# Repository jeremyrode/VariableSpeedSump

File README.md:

# VariableSpeedSump
Raspberry Pi Pico Based Variable Speed Sump Pump Controller

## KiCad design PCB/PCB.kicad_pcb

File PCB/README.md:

#  PCB

Fabricated on 8/18/2025

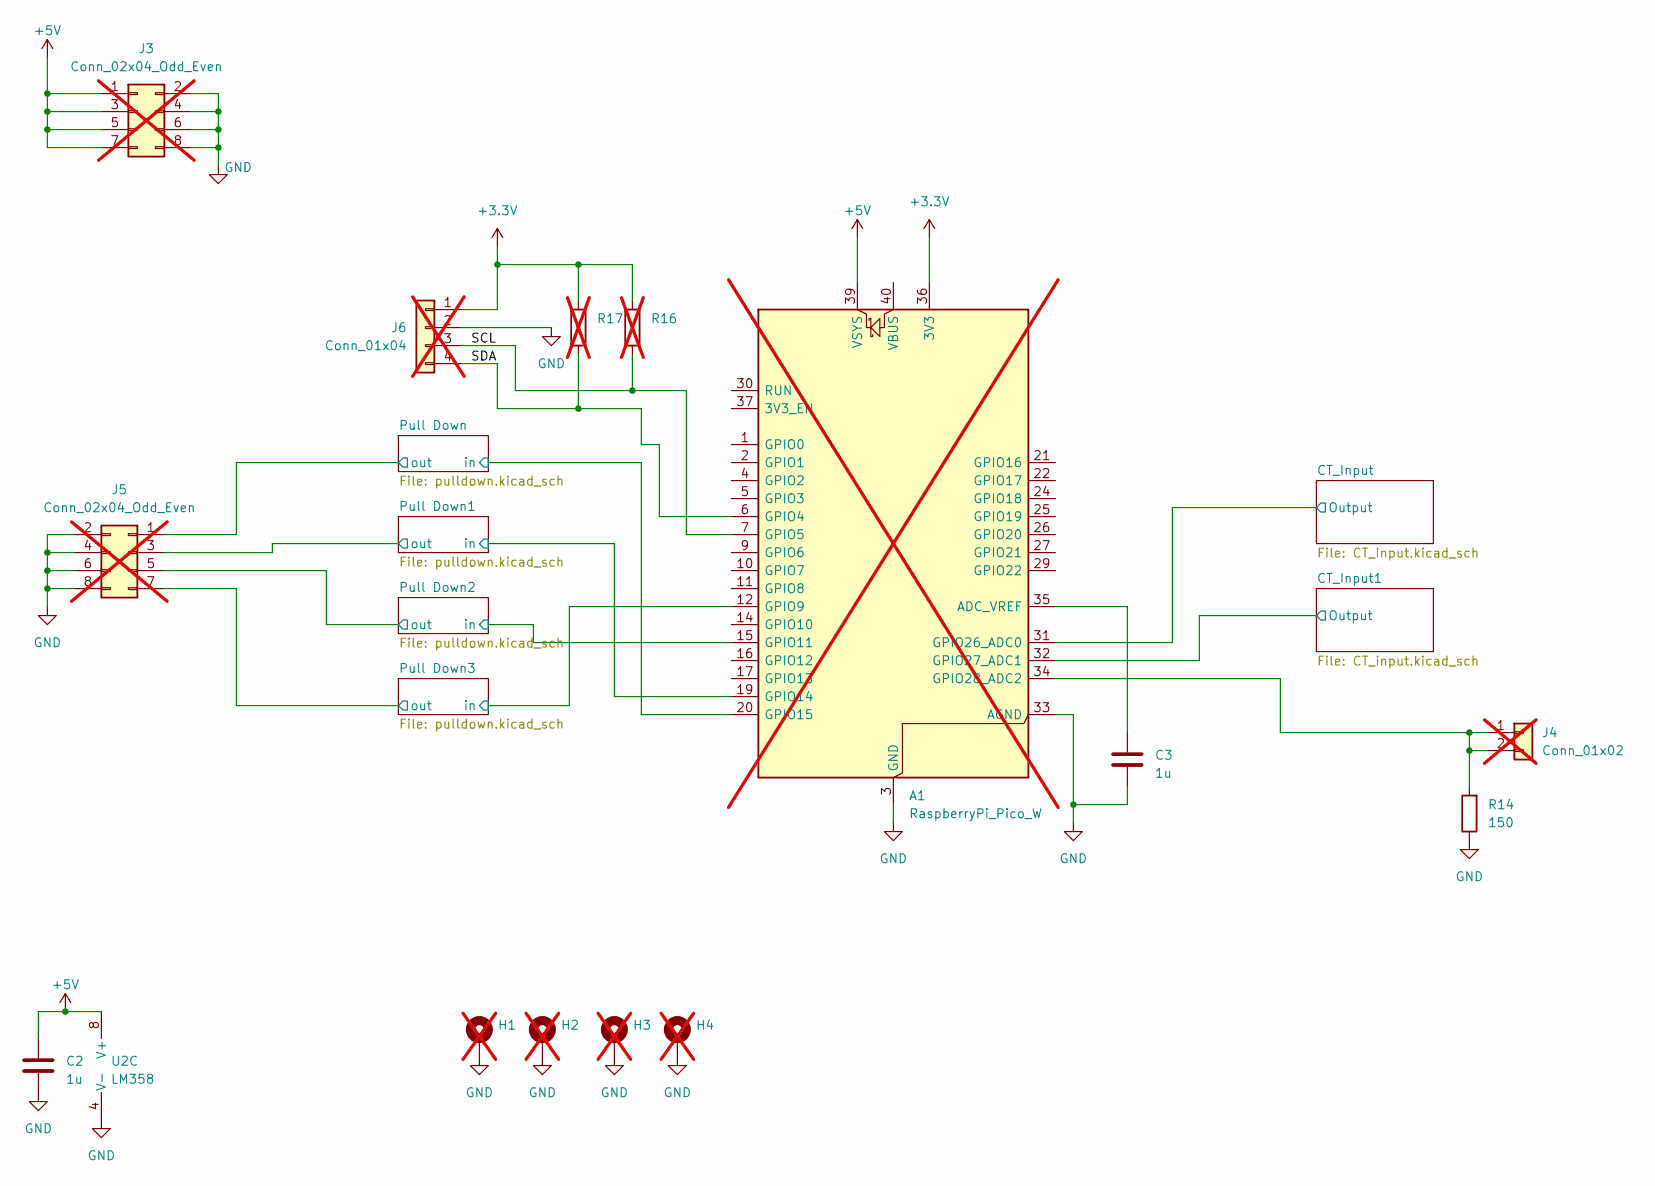
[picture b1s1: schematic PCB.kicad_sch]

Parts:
A1: RaspberryPi_Pico_W; RaspberryPi_Pico_Common_THT; not fitted
C2, C3: 1u; C_0805_2012Metric_Pad1.18x1.45mm_HandSolder
H1, H2, H3, H4: MountingHole_Pad; MountingHole_2.7mm_M2.5_Pad; not fitted
J3, J5: Conn_02x04_Odd_Even; PinHeader_2x04_P2.54mm_Vertical; not fitted
J4: Conn_01x02; PinHeader_1x02_P2.54mm_Vertical; not fitted
J6: Conn_01x04; PinHeader_1x04_P2.54mm_Vertical; not fitted
R14: 150; R_0805_2012Metric_Pad1.20x1.40mm_HandSolder
R16, R17: R_0805_2012Metric_Pad1.20x1.40mm_HandSolder; not fitted
U2: LM358; SOIC-8_3.9x4.9mm_P1.27mm

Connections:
+3.3V: A1.36 (3V3), J6.1, R16.2, R17.1
+5V: A1.39 (VSYS), C2.1, J3.1, J3.3, J3.5, J3.7, U2.8 (V+)
/CT_Input1/Output: A1.32 (GPIO27_ADC1); also elsewhere on the board
/CT_Input/Output: A1.31 (GPIO26_ADC0); also elsewhere on the board
/Pull Down1/in: A1.19 (GPIO14); also elsewhere on the board
/Pull Down1/out: J5.3; also elsewhere on the board
/Pull Down2/in: A1.15 (GPIO11); also elsewhere on the board
/Pull Down2/out: J5.5; also elsewhere on the board
/Pull Down3/in: A1.12 (GPIO9); also elsewhere on the board
/Pull Down3/out: J5.7; also elsewhere on the board
/Pull Down/in: A1.20 (GPIO15); also elsewhere on the board
/Pull Down/out: J5.1; also elsewhere on the board
/SCL: A1.7 (GPIO5), J6.3, R16.1
/SDA: A1.6 (GPIO4), J6.4, R17.2
GND: A1.3 (GND), A1.8 (GND), A1.13 (GND), A1.18 (GND), A1.23 (GND), A1.28 (GND), A1.33 (AGND), A1.38 (GND), C2.2, C3.2, H1.1, H2.1, H3.1, H4.1, J3.2, J3.4, J3.6, J3.8, J5.2, J5.4, J5.6, J5.8, J6.2, R14.1, U2.4 (V-); also elsewhere on the board
unnamed: A1.35 (ADC_VREF), C3.1
unnamed: A1.34 (GPIO28_ADC2), J4.1, J4.2, R14.2
unnamed 18: U2.7; also elsewhere on the board
unnamed 25: U2.5 (+); also elsewhere on the board
unnamed 26: U2.6 (-); also elsewhere on the board

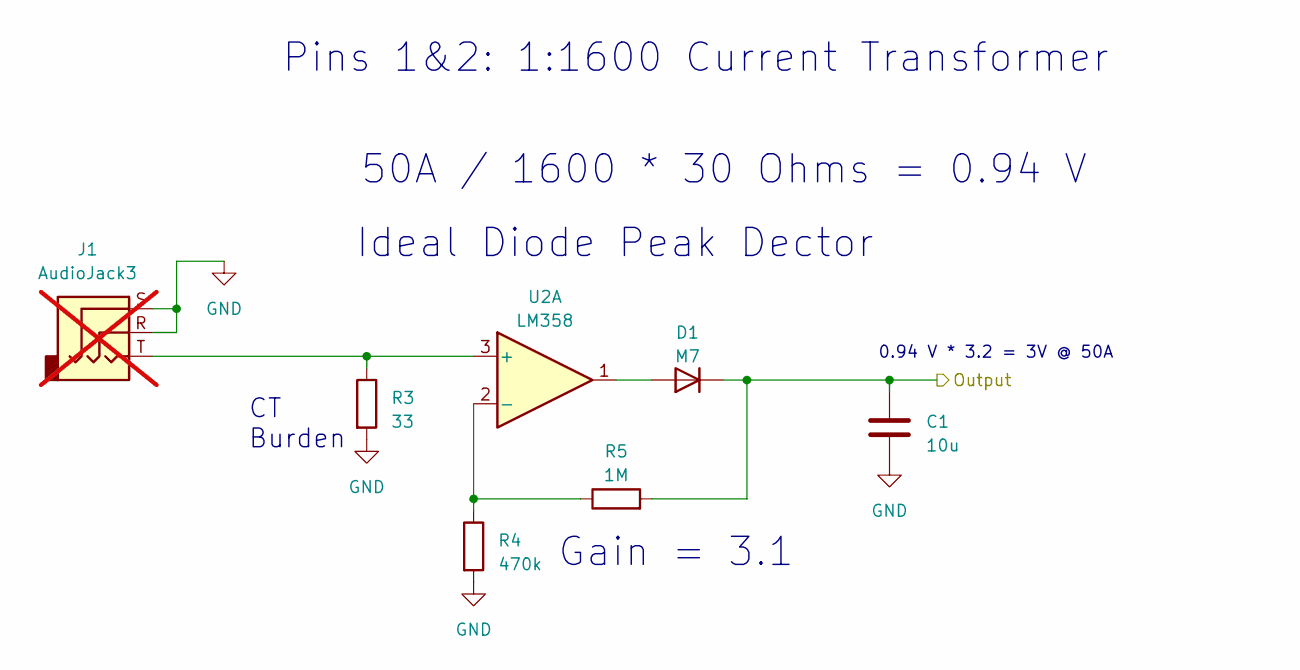
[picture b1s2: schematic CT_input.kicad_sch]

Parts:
C1: 10u; C_0805_2012Metric_Pad1.18x1.45mm_HandSolder
D1: M7; D_SMA
J1: AudioJack3; Jack_3.5mm_CUI_SJ1-3533NG_Horizontal; not fitted
R3: 33; R_0805_2012Metric_Pad1.20x1.40mm_HandSolder
R4: 470k; R_0805_2012Metric_Pad1.20x1.40mm_HandSolder
R5: 1M; R_0805_2012Metric_Pad1.20x1.40mm_HandSolder
U2: LM358; SOIC-8_3.9x4.9mm_P1.27mm

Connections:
/CT_Input/Output: C1.1, D1.1 (K), R5.2; also elsewhere on the board
GND: C1.2, J1.R, J1.S, R3.2, R4.2; also elsewhere on the board
unnamed: D1.2 (A), U2.1
unnamed 18: U2.7; also elsewhere on the board
unnamed: J1.T, R3.1, U2.3 (+)
unnamed: R4.1, R5.1, U2.2 (-)
unnamed 25: U2.5 (+); also elsewhere on the board
unnamed 26: U2.6 (-); also elsewhere on the board

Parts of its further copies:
C4: 10u; C_0805_2012Metric_Pad1.18x1.45mm_HandSolder
D2: M7; D_SMA
J2: AudioJack3; Jack_3.5mm_CUI_SJ1-3533NG_Horizontal; not fitted
R1: 33; R_0805_2012Metric_Pad1.20x1.40mm_HandSolder
R2: 470k; R_0805_2012Metric_Pad1.20x1.40mm_HandSolder
R6: 1M; R_0805_2012Metric_Pad1.20x1.40mm_HandSolder

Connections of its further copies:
/CT_Input1/Output: C4.1, D2.1 (K), R6.2; also elsewhere on the board
GND: C4.2, J2.R, J2.S, R1.2, R2.2; also elsewhere on the board
unnamed 18: D2.2 (A); also elsewhere on the board
unnamed 25: J2.T, R1.1; also elsewhere on the board
unnamed 26: R2.1, R6.1; also elsewhere on the board

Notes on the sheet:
0.94 V * 3.2 = 3V @ 50A
Gain = 3.1
Ideal Diode Peak Dector
CT Burden
50A / 1600 * 30 Ohms = 0.94 V
Pins 1&2: 1:1600 Current Transformer

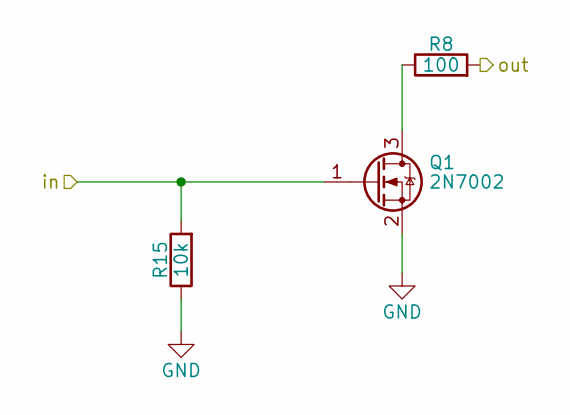
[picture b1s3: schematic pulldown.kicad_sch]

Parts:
Q1: 2N7002; SOT-23-3
R8: 100; R_0805_2012Metric_Pad1.20x1.40mm_HandSolder
R15: 10k; R_0805_2012Metric_Pad1.20x1.40mm_HandSolder

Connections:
/Pull Down/in: Q1.1 (G), R15.2; also elsewhere on the board
/Pull Down/out: R8.2; also elsewhere on the board
GND: Q1.2 (S), R15.1; also elsewhere on the board
unnamed: Q1.3 (D), R8.1

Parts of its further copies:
Q2, Q3, Q4: 2N7002; SOT-23-3
R7, R10, R12: 10k; R_0805_2012Metric_Pad1.20x1.40mm_HandSolder
R9, R11, R13: 100; R_0805_2012Metric_Pad1.20x1.40mm_HandSolder

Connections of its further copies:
/Pull Down1/in: Q2.1 (G), R7.2; also elsewhere on the board
/Pull Down1/out: R9.2; also elsewhere on the board
/Pull Down2/in: Q3.1 (G), R10.2; also elsewhere on the board
/Pull Down2/out: R11.2; also elsewhere on the board
/Pull Down3/in: Q4.1 (G), R12.2; also elsewhere on the board
/Pull Down3/out: R13.2; also elsewhere on the board
GND: Q2.2 (S), Q3.2 (S), Q4.2 (S), R7.1, R10.1, R12.1; also elsewhere on the board
unnamed: Q2.3 (D), R9.1
unnamed: Q3.3 (D), R11.1
unnamed: Q4.3 (D), R13.1

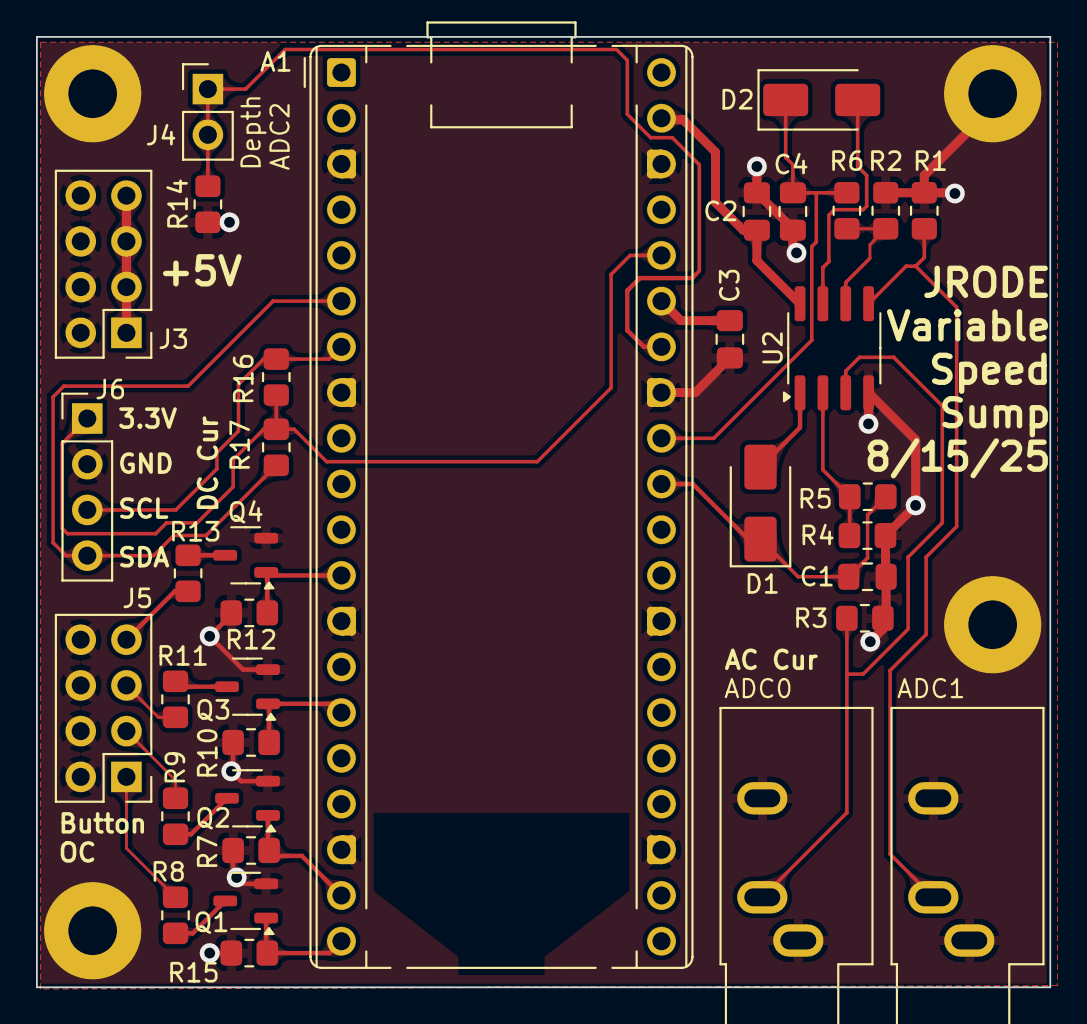
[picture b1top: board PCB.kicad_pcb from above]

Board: 4 copper layers, 56.3 x 52.8 mm, 39 parts (0 on the bottom side), 27 nets.

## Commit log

2025-08-13 inital checkin
2025-08-13 1st draft PCB
2025-08-20 First Spin of PCB
2025-08-27 inital testing
2025-08-27 org changes
2025-08-27 add functions
2025-08-27 control loop
2025-09-04 buttons work
2025-09-04 depth working, current working
2025-09-06 bucket testing successful
